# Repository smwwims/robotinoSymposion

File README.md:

# robotinoSymposion
A custom transportation / service robot based on the Festo Robotino.

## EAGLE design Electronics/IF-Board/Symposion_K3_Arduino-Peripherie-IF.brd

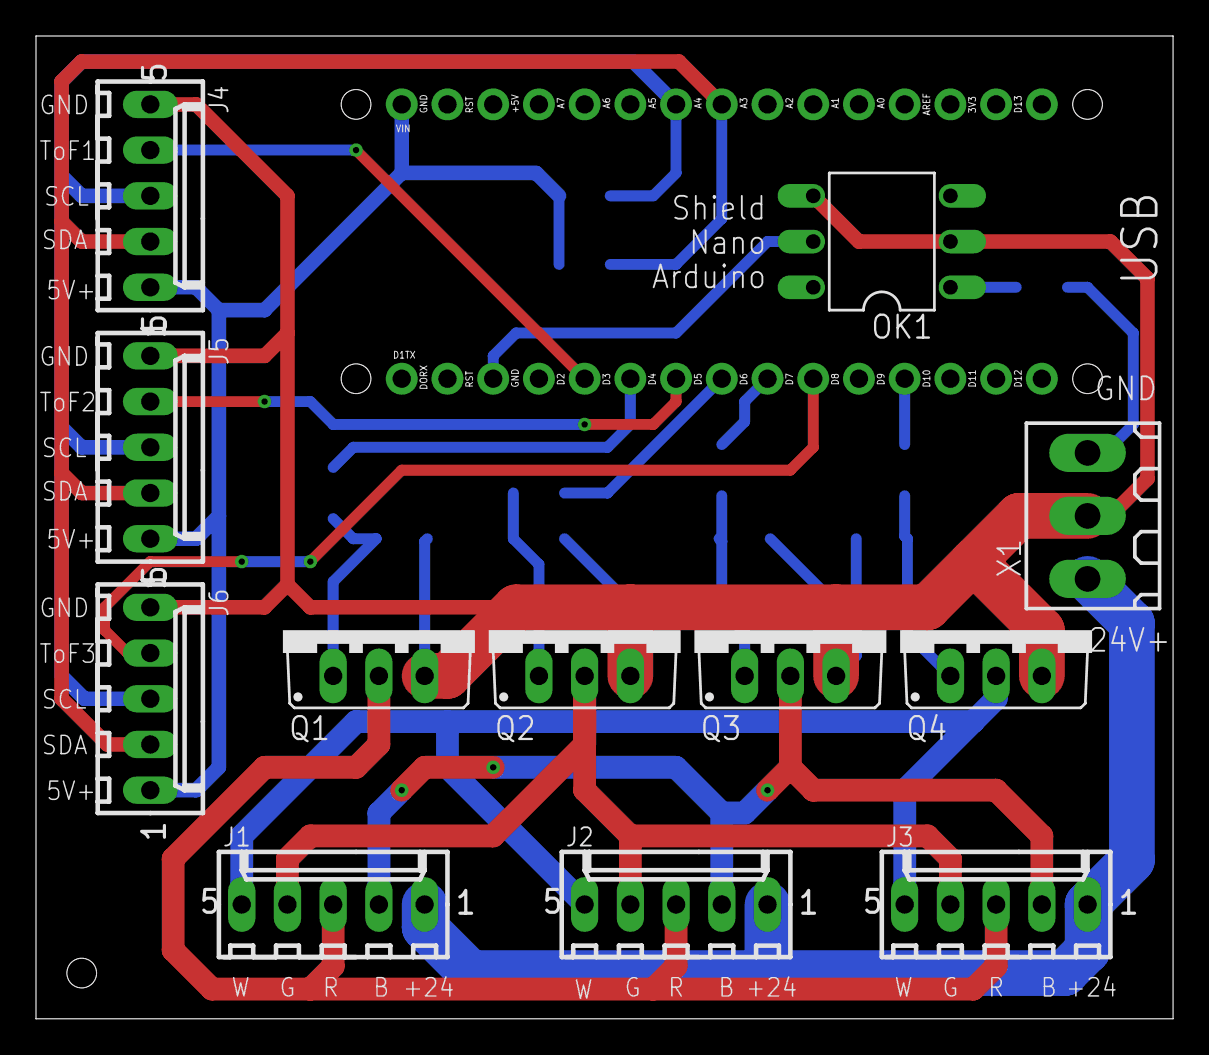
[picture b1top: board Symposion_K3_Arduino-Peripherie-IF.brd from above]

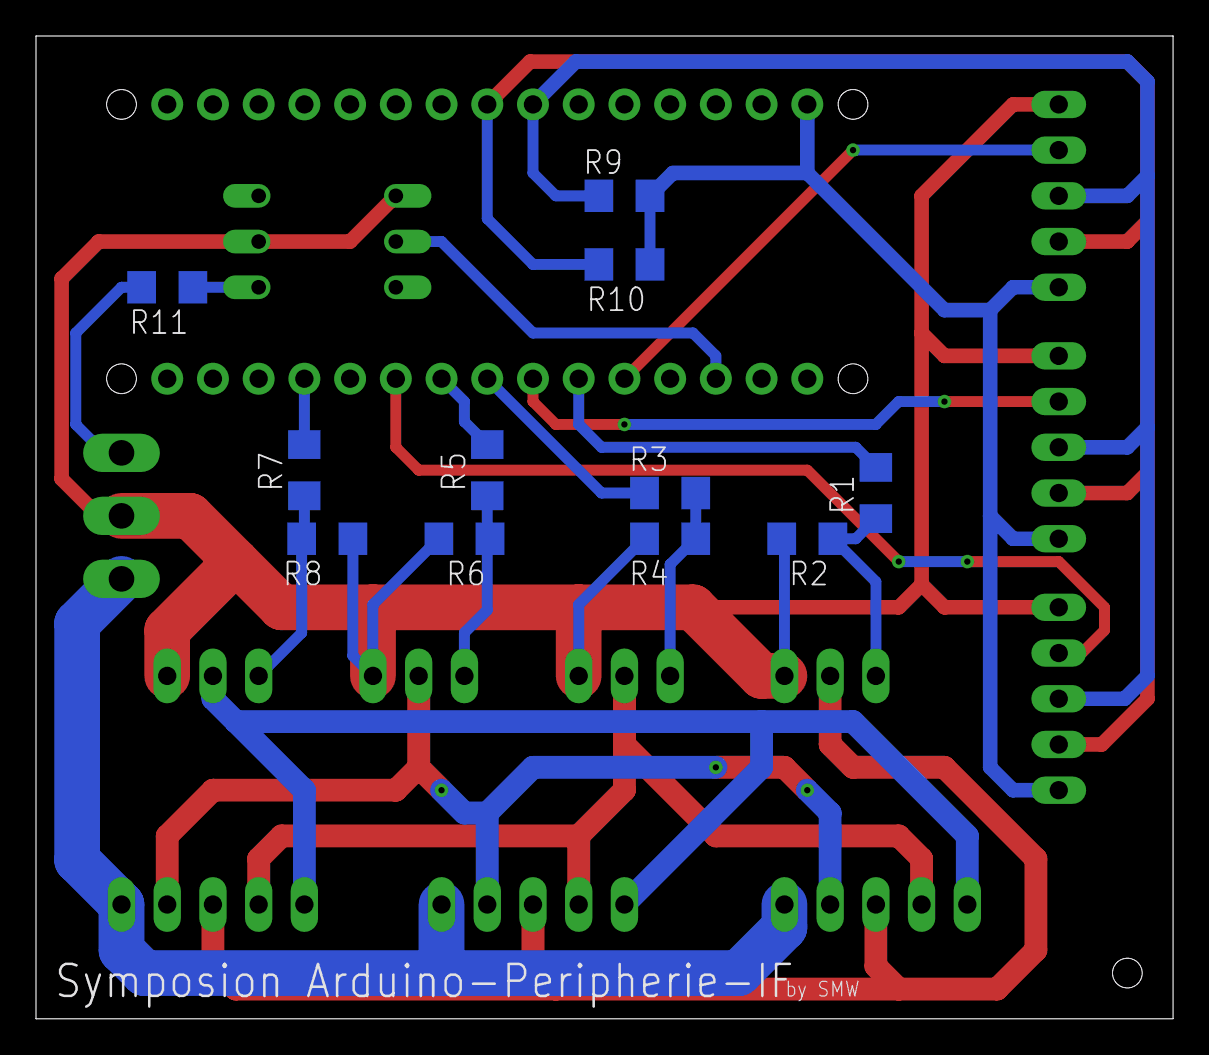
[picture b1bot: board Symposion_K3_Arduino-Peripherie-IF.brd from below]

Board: 2 copper layers, 63.2 x 54.6 mm, 24 parts (11 on the bottom side), 23 nets.

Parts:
J1, J2, J3, J4, J5, J6: 22-27-2051-05; 6410-05
OK1: CNY17F; DIL06
PCB1: 0_WSH_FAVORITES_ARDUINO_NANO
Q1, Q2, Q3, Q4: 0_WSH_FAVORITES_BUZ11BV; 0_WSH_FAVORITES_TO220BV
R1, R3, R5, R7: 1k2; R1206
R2, R4, R6, R8: 100k; R1206
R9, R10, R11: 1k8; R1206
X1: 180-3

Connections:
5V+: J4.1, J5.1, J6.1, PCB1.VIN, R9.1, R10.1
24V: J1.1, J2.1, J3.1, X1.1
BOUT: J1.2, J2.2, J3.2, Q3.D
BPWM: PCB1.D6, R5.2
GND: J4.5, J5.5, J6.5, OK1.2, OK1.4, Q1.S, Q2.S, Q3.S, Q4.S, R2.2, R4.2, R6.2, R8.2, X1.2
GOUT: J1.4, J2.4, J3.4, Q2.D
GPWM: PCB1.D5, R3.2
unnamed: Q1.G, R1.1, R2.1
unnamed: OK1.1, R11.1
unnamed: Q2.G, R3.1, R4.1
unnamed: Q3.G, R5.1, R6.1
unnamed: Q4.G, R7.1, R8.1
ROUT: J1.3, J2.3, J3.3, Q1.D
RPWM: PCB1.D3, R1.2
RST: OK1.5, PCB1.RST
SCL: J4.3, J5.3, J6.3, PCB1.A5, R9.2
SDA: J4.2, J5.2, J6.2, PCB1.A4, R10.2
SYS: R11.2, X1.3
TOF1: J4.4, PCB1.D2
TOF2: J5.4, PCB1.D4
TOF3: J6.4, PCB1.D7
WOUT: J1.5, J2.5, J3.5, Q4.D
WPWM: PCB1.D9, R7.2

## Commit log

2024-06-18 Create Software Folder
2024-06-18 Create Electronics Folder
2024-06-19 Create IF-Board Folder
2024-06-19 Add IF-Board Schematic v1.0
    3 x Light Strip Output (RGBW)
    3 x ToF Input (VL531LX)
    for Arduino Nano
2024-06-19 IF-Board pcb design v1.0
2024-06-19 Schematic v1.6
